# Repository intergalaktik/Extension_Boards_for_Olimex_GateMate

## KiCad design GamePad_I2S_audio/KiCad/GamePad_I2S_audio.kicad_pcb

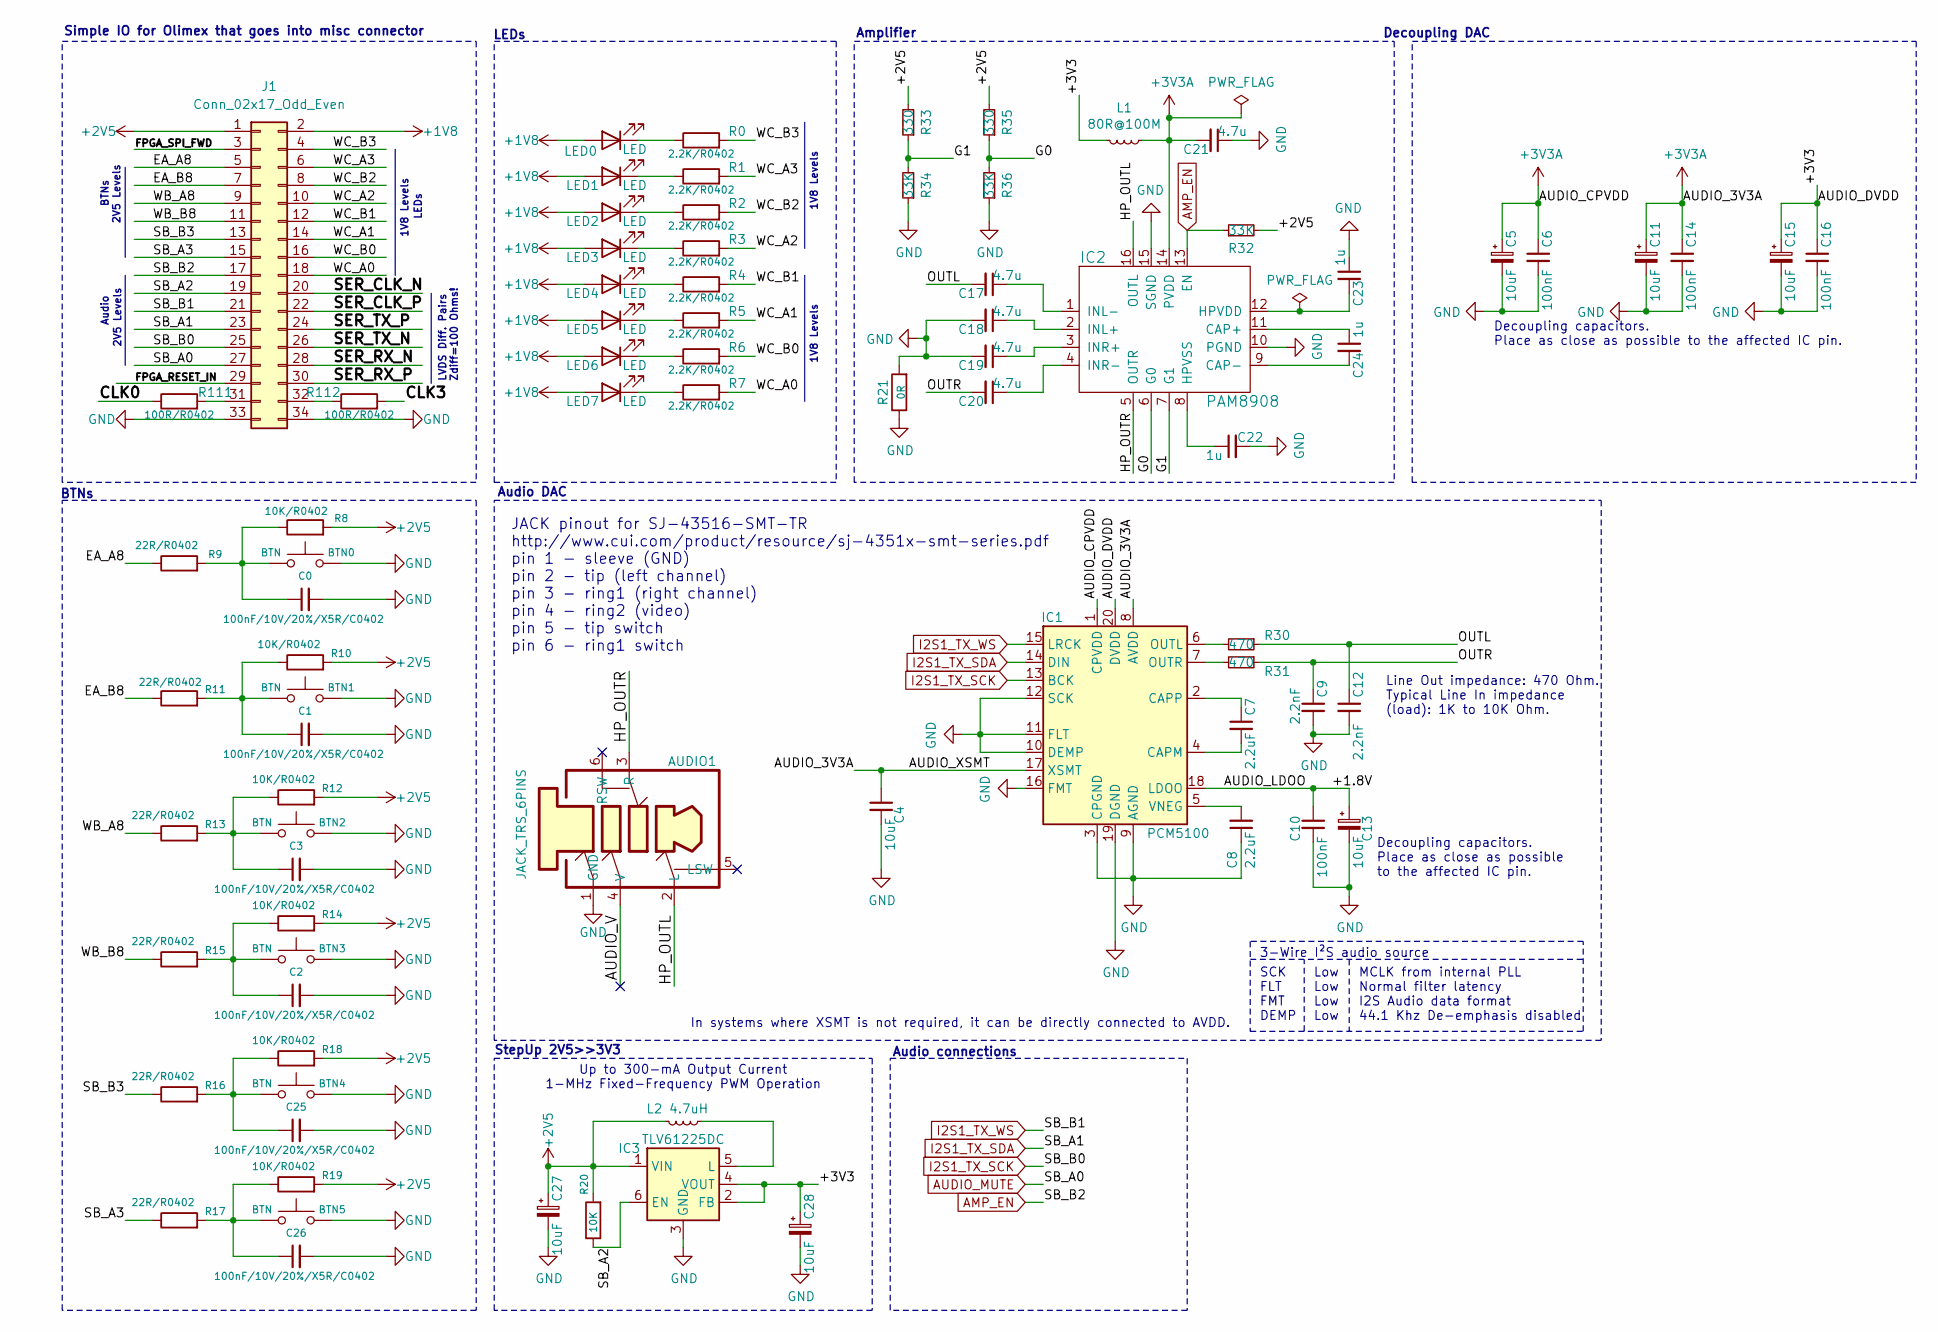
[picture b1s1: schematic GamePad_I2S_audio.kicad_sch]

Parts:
AUDIO1: JACK_TRS_6PINS; CUI_SJ-43516-SMT; MPN SJ-43516-SMT-TR; Mouser 490-SJ43515TS-SMT-TR
BTN0, BTN1, BTN2, BTN3, BTN4, BTN5: BTN; SW_SPST_B3S-1000
C0, C1, C2, C3, C25, C26: 100nF/10V/20%/X5R/C0402; C_0402_1005Metric
C4, C5, C11, C13, C15, C27, C28: 10uF; C_0603_1608Metric
C6, C10, C14, C16: 100nF; C_0402_1005Metric
C7, C8: 2.2uF; C_0402_1005Metric
C9, C12: 2.2nF; C_0402_1005Metric
C17, C18, C19, C20, C21: 4.7u; C_0603_1608Metric
C22, C23, C24: 1u; C_0603_1608Metric
IC1: PCM5100; TSSOP-20_4.4x6.5mm_P0.65mm
IC2: PAM8908; QFN-16-1EP_3x3mm_P0.5mm_EP1.7x1.7mm_ThermalVias
IC3: TLV61225DC; SOT-363_SC-70-6
J1: Conn_02x17_Odd_Even; PinSocket_2x17_P2.54mm_Vertical_SMD
L1: 80R@100M; L_0603_1608Metric
L2: 4.7uH; L_0603_1608Metric
LED0, LED1, LED2, LED3, LED4, LED5, LED6, LED7: LED; LED_0603_1608Metric
R0, R1, R2, R3, R4, R5, R6, R7: 2.2K/R0402; R_0402_1005Metric
R8, R10, R12, R14, R18, R19: 10K/R0402; R_0402_1005Metric
R9, R11, R13, R15, R16, R17: 22R/R0402; R_0402_1005Metric
R20: 10K; R_0402_1005Metric; MPN RC0603FR-071K1L; Digikey P1.10KHCT-ND
R21: 0R; R_0402_1005Metric
R30, R31: 470; R_0402_1005Metric
R32, R34, R36: 33K; R_0402_1005Metric
R33, R35: 330; R_0402_1005Metric
R111, R112: 100R/R0402; R_0402_1005Metric

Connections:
+1V8: J1.2, LED0.2 (A), LED1.2 (A), LED2.2 (A), LED3.2 (A), LED4.2 (A), LED5.2 (A), LED6.2 (A), LED7.2 (A)
+2V5: C27.1, IC3.1 (VIN), J1.1, L2.2, R8.2, R10.2, R12.2, R14.2, R18.2, R19.2, R20.2, R32.2, R33.2, R35.2
+3V3A: C4.1, C5.1, C6.1, C11.1, C14.1, C21.2, IC1.1 (CPVDD), IC1.8 (AVDD), IC1.17 (XSMT), IC2.14 (PVDD), L1.1
/+1.8V: C10.1, C13.1, IC1.18 (LDOO)
/+3V3: C15.1, C16.1, C28.1, IC1.20 (DVDD), IC3.2 (FB), IC3.4 (VOUT), L1.2
/AUDIO_V: AUDIO1.4 (V)
/CLK0: R111.1
/CLK3: R112.2
/EA_A8: J1.5, R9.1
/EA_B8: J1.7, R11.1
/FPGA_RESET_IN: J1.29
/FPGA_SPI_FWD: J1.3
/G0: IC2.6 (G0), R35.1, R36.2
/G1: IC2.7 (G1), R33.1, R34.2
/HP_OUTL: AUDIO1.2 (L), IC2.16 (OUTL)
/HP_OUTR: AUDIO1.3 (R), IC2.5 (OUTR)
/OUTL: C12.1, C17.2, R30.1
/OUTR: C9.1, C20.2, R31.1
/SB_A2: IC3.6 (EN), J1.19, R20.1
/SB_A3: J1.15, R17.1
/SB_B3: J1.13, R16.1
/SER_CLK_N: J1.20
/SER_CLK_P: J1.22
/SER_RX_N: J1.28
/SER_RX_P: J1.30
/SER_TX_N: J1.26
/SER_TX_P: J1.24
/WB_A8: J1.9, R13.1
/WB_B8: J1.11, R15.1
/WC_A0: J1.18, R7.2
/WC_A1: J1.14, R5.2
/WC_A2: J1.10, R3.2
/WC_A3: J1.6, R1.2
/WC_B0: J1.16, R6.2
/WC_B1: J1.12, R4.2
/WC_B2: J1.8, R2.2
/WC_B3: J1.4, R0.2
AMP_EN: IC2.13 (EN), J1.17, R32.1
AUDIO_MUTE: J1.27
I2S1_TX_SCK: IC1.13 (BCK), J1.25
I2S1_TX_SDA: IC1.14 (DIN), J1.23
I2S1_TX_WS: IC1.15 (LRCK), J1.21
unnamed: BTN0.1, C0.1, R8.1, R9.2
unnamed: BTN1.1, C1.1, R10.1, R11.2
unnamed: BTN2.1, C3.1, R12.1, R13.2
unnamed: BTN3.1, C2.1, R14.1, R15.2
unnamed: BTN4.1, C25.1, R16.2, R18.1
unnamed: BTN5.1, C26.1, R17.2, R19.1
unnamed: C7.2, IC1.4 (CAPM)
unnamed: C7.1, IC1.2 (CAPP)
unnamed: IC1.6 (OUTL), R30.2
unnamed: IC1.7 (OUTR), R31.2
unnamed: C8.2, IC1.5 (VNEG)
unnamed: C24.1, IC2.11 (CAP+)
unnamed: C24.2, IC2.9 (CAP-)
unnamed: C23.2, IC2.12 (HPVDD)
unnamed: C22.1, IC2.8 (HPVSS)
unnamed: C18.1, IC2.2 (INL+)
unnamed: C17.1, IC2.1 (INL-)
unnamed: C19.1, IC2.3 (INR+)
unnamed: C20.1, IC2.4 (INR-)
unnamed: IC3.5 (L), L2.1
unnamed: J1.31, R111.2
unnamed: J1.32, R112.1
unnamed: LED0.1 (K), R0.1
unnamed: LED1.1 (K), R1.1
unnamed: LED2.1 (K), R2.1
unnamed: LED3.1 (K), R3.1
unnamed: LED4.1 (K), R4.1
unnamed: LED5.1 (K), R5.1
unnamed: LED6.1 (K), R6.1
unnamed: LED7.1 (K), R7.1

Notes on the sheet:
2V5 Levels
1V8 Levels
Up to 300-mA Output Current 1-MHz Fixed-Frequency PWM Operation
Audio connections
Audio DAC
Line Out impedance: 470 Ohm. Typical Line In impedance (load): 1K to 10K Ohm.
StepUp 2V5>>3V3
BTNs
In systems where XSMT is not required, it can be directly connected to AVDD.
3-Wire I²S audio source
Low Low Low Low
Decoupling capacitors. Place as close as possible to the affected IC pin.
Amplifier
JACK pinout for SJ-43516-SMT-TR http://www.cui.com/product/resource/sj-4351x-smt-series.pdf pin 1 - sleeve (GND) pin 2 - tip (left channel) pin 3 - ring1 (right channel) pin 4 - ring2 (video) pin 5 - tip switch pin 6 - ring1 switch
LVDS Diff. Pairs Zdiff=100 Ohms!
SCK FLT FMT DEMP
MCLK from internal PLL Normal filter latency I2S Audio data format 44.1 Khz De-emphasis disabled
Audio
LEDs
Simple IO for Olimex that goes into misc connector
Decoupling capacitors. Place as close as possible to the affected IC pin.
Decoupling DAC

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
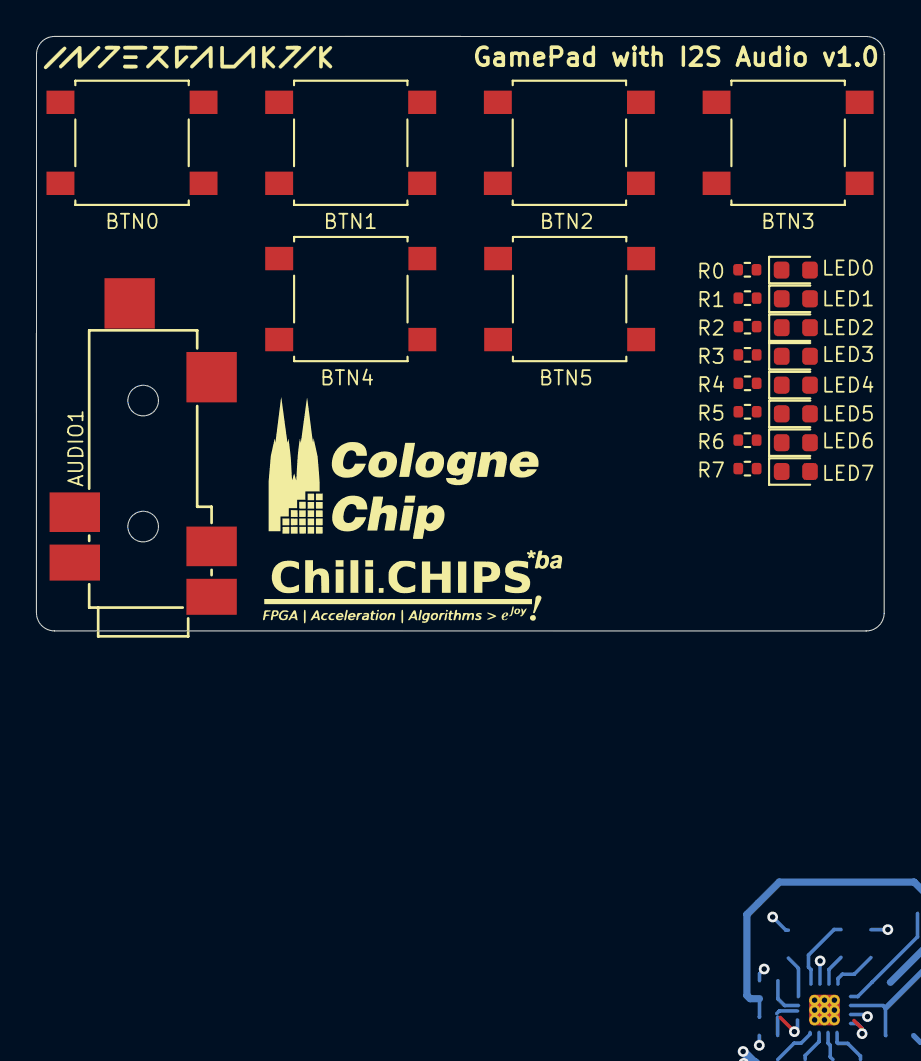
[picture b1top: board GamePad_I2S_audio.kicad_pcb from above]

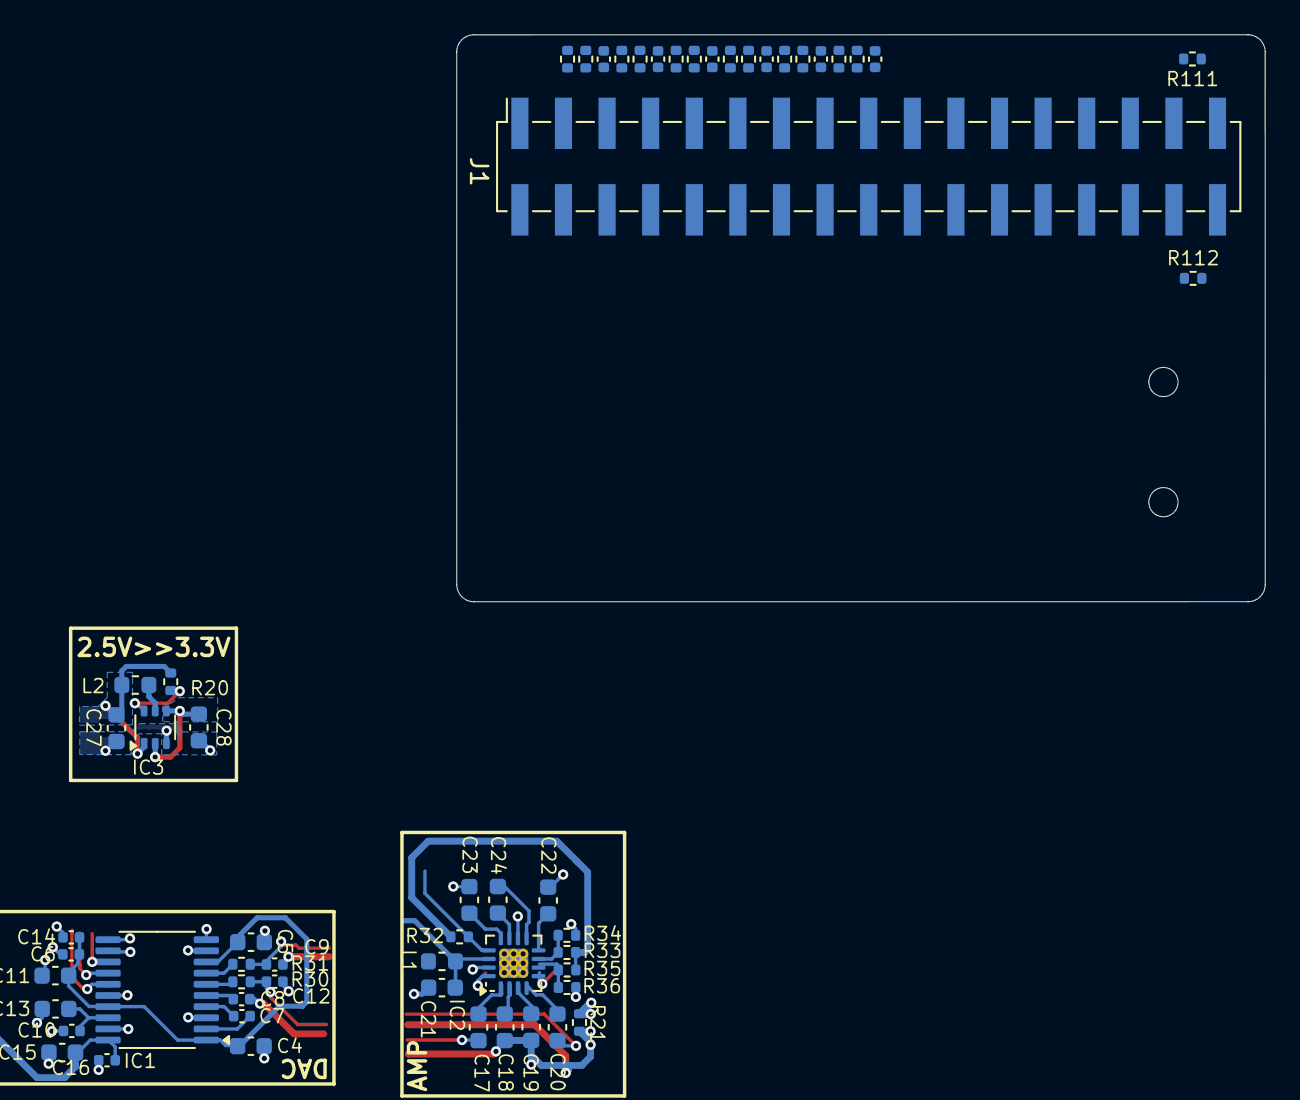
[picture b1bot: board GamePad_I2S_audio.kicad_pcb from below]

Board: 4 copper layers, 47.1 x 33.0 mm, 81 parts (58 on the bottom side), 62 nets.

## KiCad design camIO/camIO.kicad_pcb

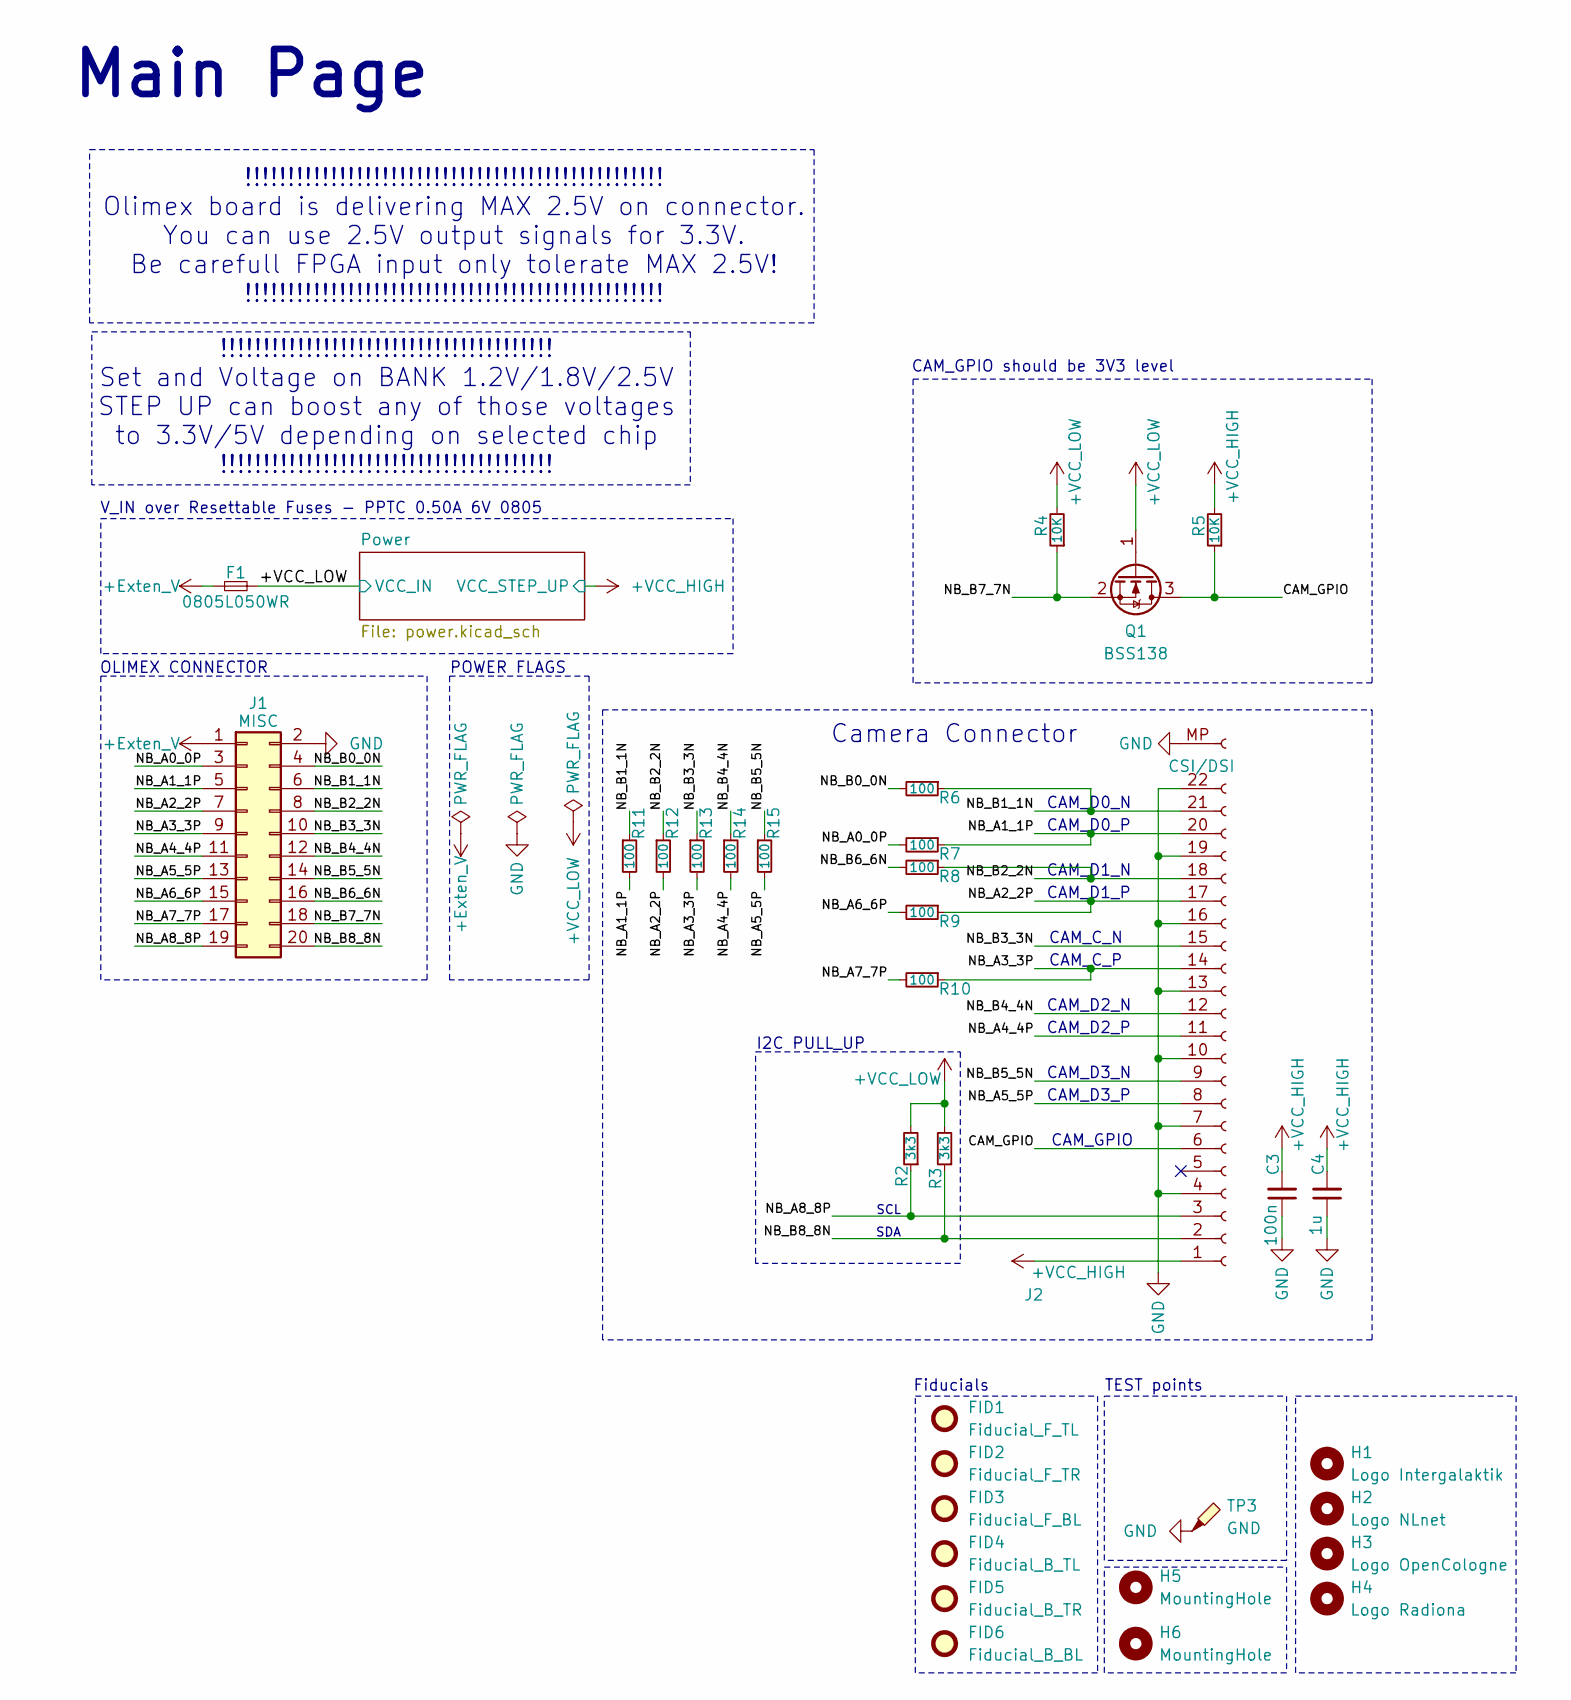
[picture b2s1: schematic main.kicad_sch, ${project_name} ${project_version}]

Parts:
C3: 100n; C_0402_1005Metric
C4: 1u; C_0603_1608Metric
F1: 0805L050WR; Fuse_0805_2012Metric
FID1: Fiducial_F_TL; Fiducial_0.5mm_Mask1mm
FID2: Fiducial_F_TR; Fiducial_0.5mm_Mask1mm
FID3: Fiducial_F_BL; Fiducial_0.5mm_Mask1mm
FID4: Fiducial_B_TL; Fiducial_0.5mm_Mask1mm
FID5: Fiducial_B_TR; Fiducial_0.5mm_Mask1mm
FID6: Fiducial_B_BL; Fiducial_0.5mm_Mask1mm
H1: Logo Intergalaktik; intergalaktik
H2: Logo NLnet; nlnet
H3: Logo OpenCologne; open_cologne_small
H4: Logo Radiona; radiona_small
H5, H6: MountingHole; MountingHole_2.2mm_M2
J1: MISC; PinSocket_2x10_P2.54mm_Vertical_SMD
J2: CSI/DSI; Hirose_FH12-22S-0.5SH_1x22-1MP_P0.50mm_Horizontal; Part Description 22 Position FFC, FPC Connector Contacts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
Q1: BSS138; SOT-23
R2, R3: 3k3; R_0402_1005Metric; MPN RC0603FR-071K1L; Mouser 603-RC0603FR-071K1L
R4, R5: 10K; R_0402_1005Metric; MPN RC0603FR-071K1L; Mouser 603-RC0603FR-071K1L
R6, R7, R8, R9, R10, R11, R12, R13, R14, R15: 100; R_0402_1005Metric; MPN RC0603FR-071K1L; Mouser 603-RC0603FR-071K1L
TP3: GND; TestPoint_Pad_D1.0mm

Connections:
+Exten_V: F1.1, J1.1
+VCC_HIGH: C3.2, C4.2, J2.1, R5.2; also elsewhere on the board
+VCC_LOW: F1.2, Q1.1 (G), R2.2, R3.2, R4.2; also elsewhere on the board
/Main Sheet/CAM_GPIO: J2.6, Q1.3 (D), R5.1
/Main Sheet/NB_A0_0P: J1.3, R7.2
/Main Sheet/NB_A1_1P: J1.5, J2.20, R7.1, R11.2
/Main Sheet/NB_A2_2P: J1.7, J2.17, R9.1, R12.2
/Main Sheet/NB_A3_3P: J1.9, J2.14, R10.1, R13.2
/Main Sheet/NB_A4_4P: J1.11, J2.11, R14.2
/Main Sheet/NB_A5_5P: J1.13, J2.8, R15.2
/Main Sheet/NB_A6_6P: J1.15, R9.2
/Main Sheet/NB_A7_7P: J1.17, R10.2
/Main Sheet/NB_A8_8P: J1.19, J2.3, R2.1
/Main Sheet/NB_B0_0N: J1.4, R6.2
/Main Sheet/NB_B1_1N: J1.6, J2.21, R6.1, R11.1
/Main Sheet/NB_B2_2N: J1.8, J2.18, R8.1, R12.1
/Main Sheet/NB_B3_3N: J1.10, J2.15, R13.1
/Main Sheet/NB_B4_4N: J1.12, J2.12, R14.1
/Main Sheet/NB_B5_5N: J1.14, J2.9, R15.1
/Main Sheet/NB_B6_6N: J1.16, R8.2
/Main Sheet/NB_B7_7N: J1.18, Q1.2 (S), R4.1
/Main Sheet/NB_B8_8N: J1.20, J2.2, R3.1
GND: C3.1, C4.1, J1.2, J2.4, J2.7, J2.10, J2.13, J2.16, J2.19, J2.22, J2.MP, TP3.1; also elsewhere on the board

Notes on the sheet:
Camera Connector
CAM_D1_N
TEST points
I2C PULL_UP
POWER FLAGS
V_IN over Resettable Fuses - PPTC 0.50A 6V 0805
!!!!!!!!!!!!!!!!!!!!!!!!!!!!!!!!!!!!!!!!!!!!!!!!! Olimex board is delivering MAX 2.5V on connector. You can use 2.5V output signals for 3.3V. Be carefull FPGA input only tolerate MAX 2.5V! !!!!!!!!!!!!!!!!!!!!!!!!!!!!!!!!!!!!!!!!!!!!!!!!!
CAM_D0_N
CAM_GPIO should be 3V3 level
CAM_D1_P
SCL
Fiducials
CAM_D0_P
CAM_D2_P
CAM_GPIO
CAM_D3_P
CAM_C_N
CAM_D2_N
OLIMEX CONNECTOR
CAM_D3_N
SDA
CAM_C_P
Main Page
!!!!!!!!!!!!!!!!!!!!!!!!!!!!!!!!!!!!!!! Set and Voltage on BANK 1.2V/1.8V/2.5V STEP UP can boost any of those voltages to 3.3V/5V depending on selected chip !!!!!!!!!!!!!!!!!!!!!!!!!!!!!!!!!!!!!!!

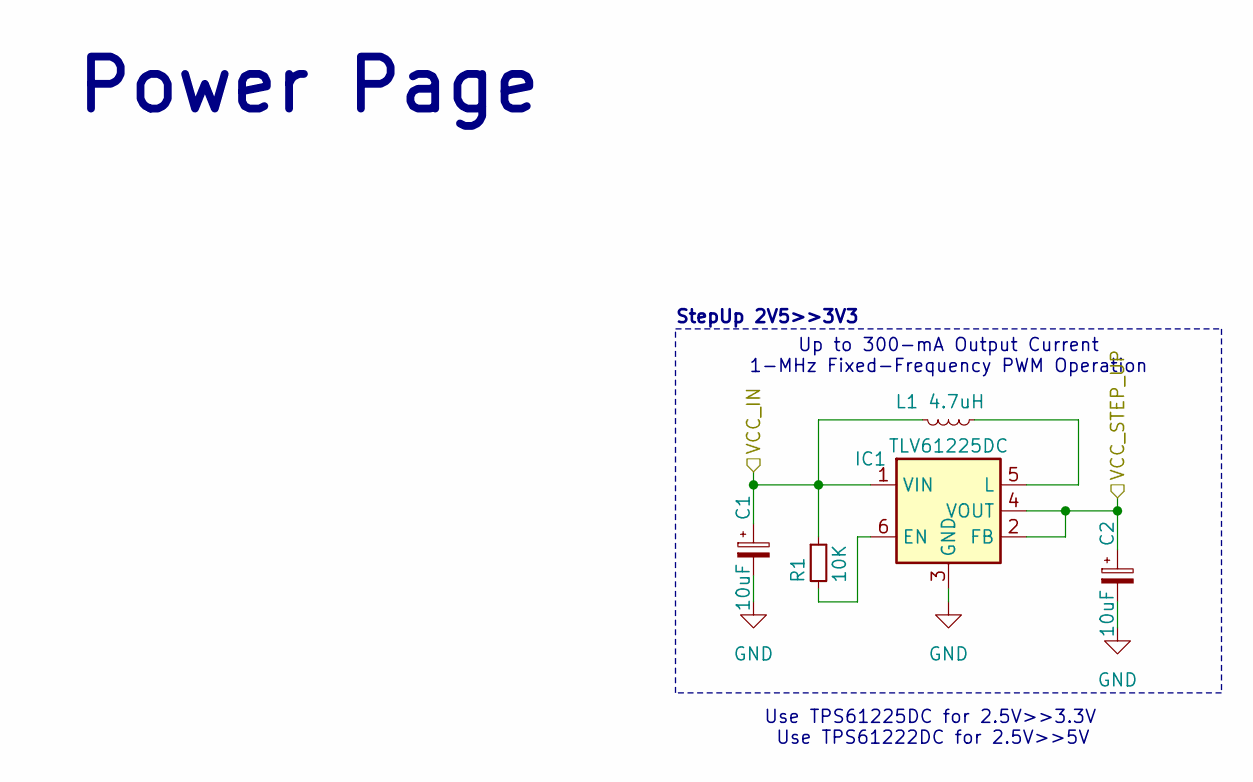
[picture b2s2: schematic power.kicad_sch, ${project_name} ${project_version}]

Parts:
C1, C2: 10uF; C_0603_1608Metric
IC1: TLV61225DC; SOT-363_SC-70-6
L1: 4.7uH; L_0603_1608Metric
R1: 10K; R_0402_1005Metric; MPN RC0603FR-071K1L; Mouser 603-RC0603FR-071K1L

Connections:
+VCC_HIGH: C2.1, IC1.2 (FB), IC1.4 (VOUT); also elsewhere on the board
+VCC_LOW: C1.1, IC1.1 (VIN), L1.2, R1.1; also elsewhere on the board
GND: C1.2, C2.2, IC1.3 (GND); also elsewhere on the board
unnamed: IC1.6 (EN), R1.2
unnamed: IC1.5 (L), L1.1

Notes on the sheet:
Up to 300-mA Output Current 1-MHz Fixed-Frequency PWM Operation
Use TPS61222DC for 2.5V>>5V
Power Page
StepUp 2V5>>3V3
Use TPS61225DC for 2.5V>>3.3V

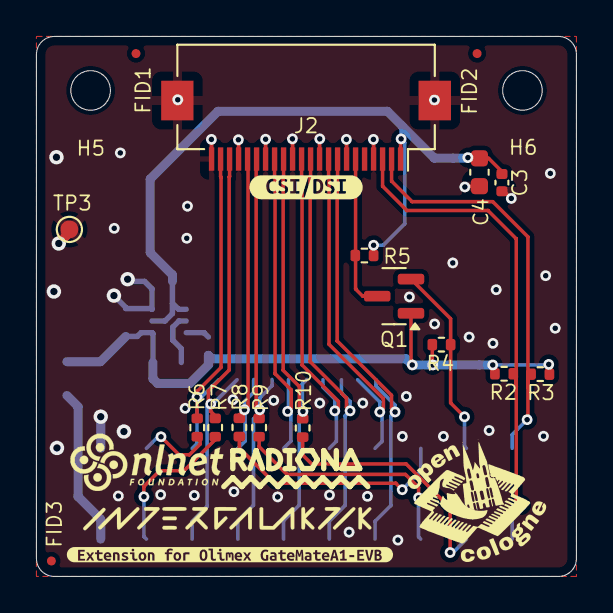
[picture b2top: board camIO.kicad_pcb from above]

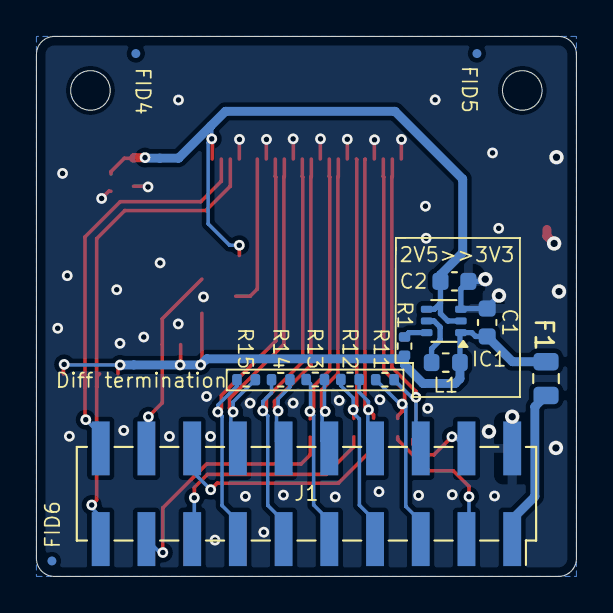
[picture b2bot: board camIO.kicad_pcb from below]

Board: 4 copper layers, 30.0 x 30.0 mm, 40 parts (15 on the bottom side), 25 nets.

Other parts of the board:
kibuzzard-674D68C8: G***; kibuzzard-674D68C8
kibuzzard-67584A5F: G***; kibuzzard-67584A5F

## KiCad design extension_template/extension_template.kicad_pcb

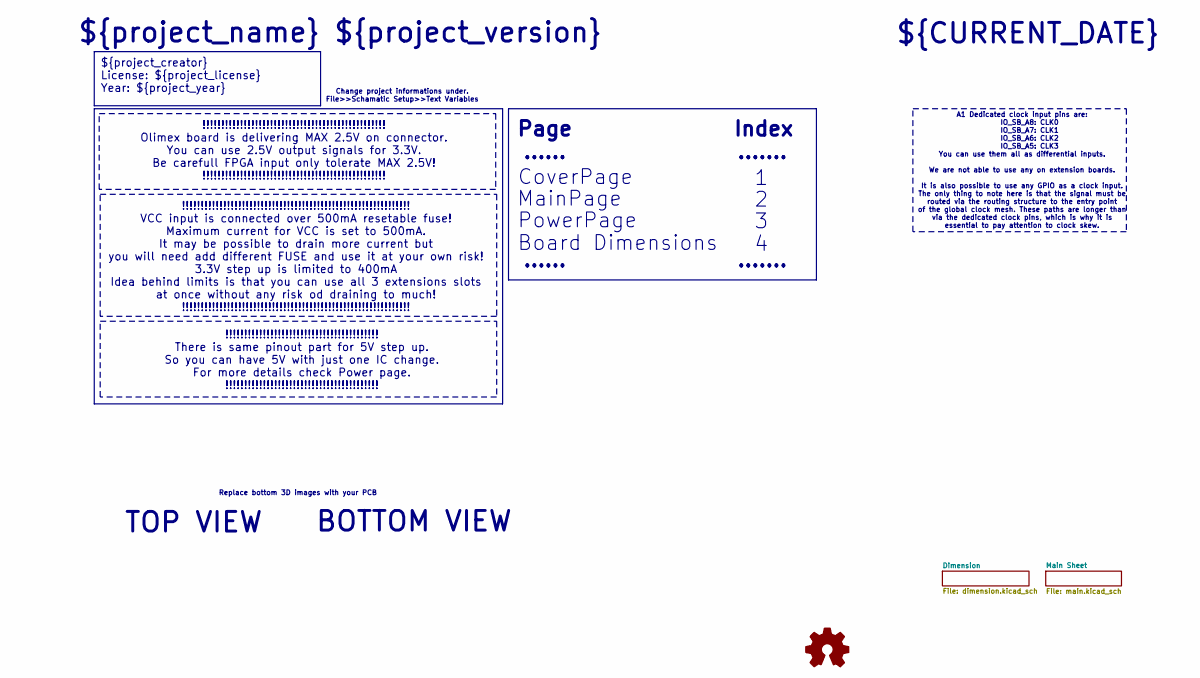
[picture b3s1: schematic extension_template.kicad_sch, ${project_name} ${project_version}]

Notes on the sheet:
${project_creator} License: ${project_license} Year: ${project_year}
BOTTOM VIEW
Replace bottom 3D images with your PCB
Index
!!!!!!!!!!!!!!!!!!!!!!!!!!!!!!!!!!!!!!!!!!!!!!!!!!!!!!!!!!!!! VCC input is connected over 500mA resetable fuse! Maximum current for VCC is set to 500mA. It may be possible to drain more current but you will need add different FUSE and use it at your own risk! 3.3V step up is limited to 400mA Idea b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
!!!!!!!!!!!!!!!!!!!!!!!!!!!!!!!!!!!!!!!!!!!!!!!!! Olimex board is delivering MAX 2.5V on connector. You can use 2.5V output signals for 3.3V. Be carefull FPGA input only tolerate MAX 2.5V! !!!!!!!!!!!!!!!!!!!!!!!!!!!!!!!!!!!!!!!!!!!!!!!!!
!!!!!!!!!!!!!!!!!!!!!!!!!!!!!!!!!!!!!!!!! There is same pinout part for 5V step up. So you can have 5V with just one IC change. For more details check Power page. !!!!!!!!!!!!!!!!!!!!!!!!!!!!!!!!!!!!!!!!!
......
PowerPage
Change project informations under. File>>Schamatic Setup>>Text Variables
.......
A1 Dedicated clock input pins are: IO_SB_A8: CLK0 IO_SB_A7: CLK1 IO_SB_A6: CLK2 IO_SB_A5: CLK3 You can use them all as differential inputs. We are not able to use any on extension boards. It is also possible to use any GPIO as a clock input. The only thing to note here is that the signal must be ro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
CoverPage
Board Dimensions
MainPage
${CURRENT_DATE}
${project_name} ${project_version}
TOP VIEW
Page

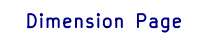
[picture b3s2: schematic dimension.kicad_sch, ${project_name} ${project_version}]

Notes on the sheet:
Dimension Page

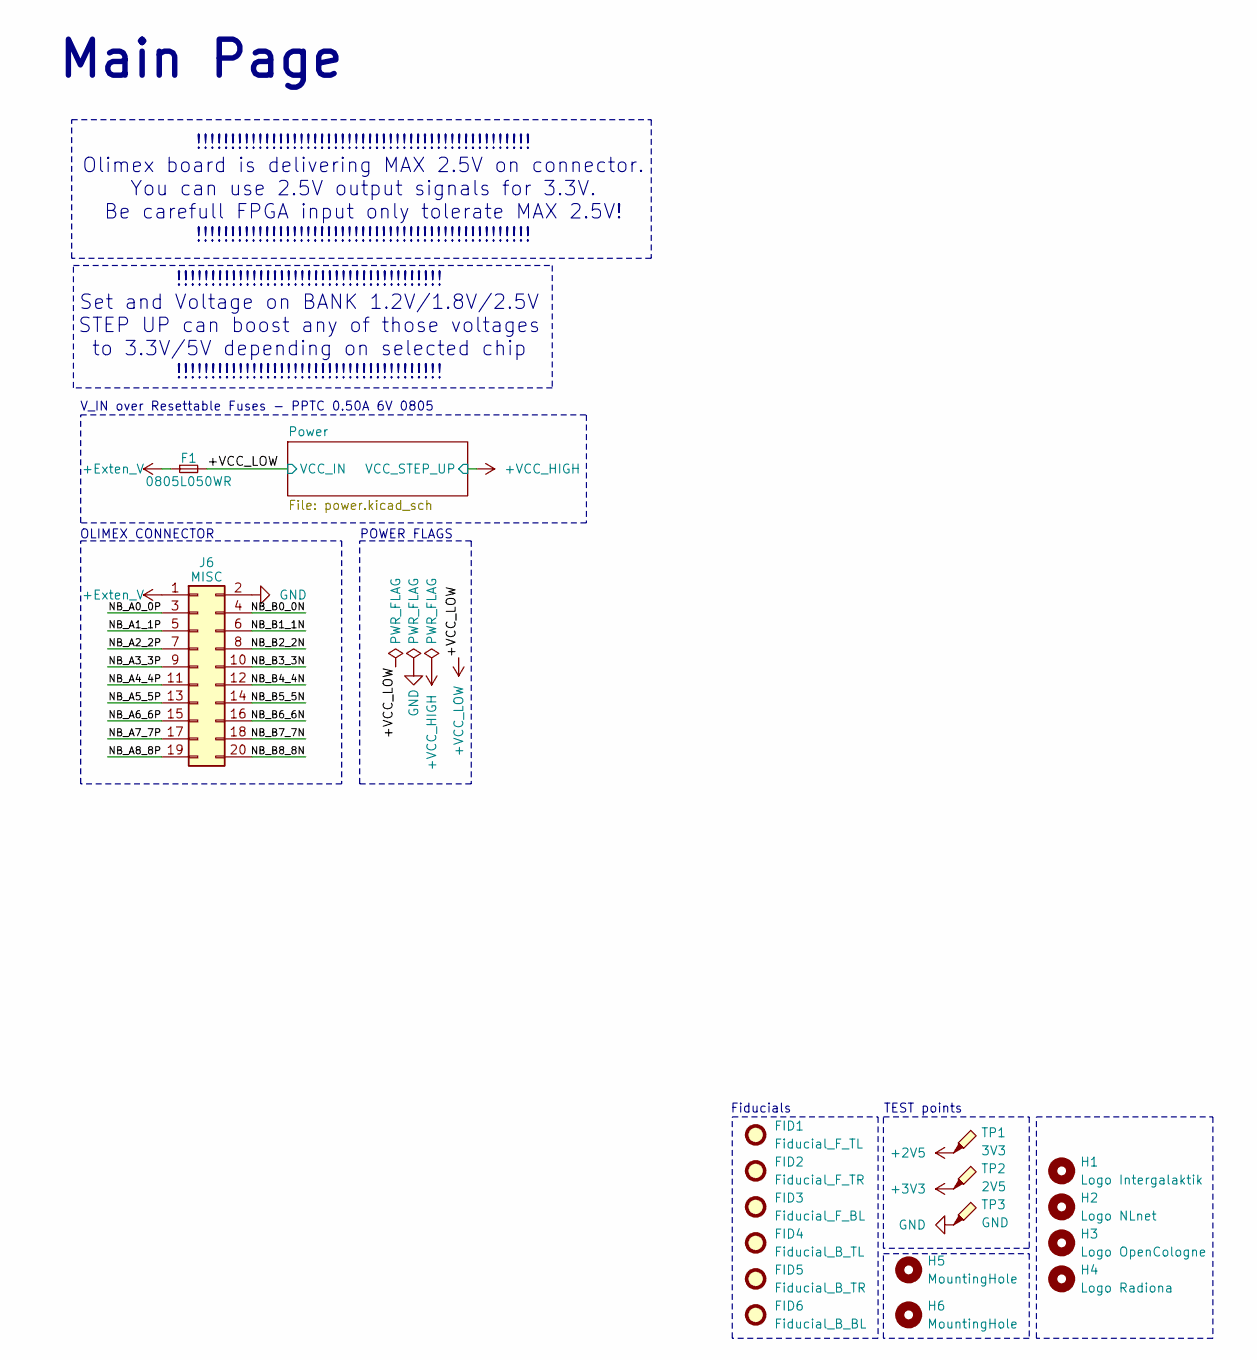
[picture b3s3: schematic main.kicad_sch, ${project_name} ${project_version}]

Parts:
F1: 0805L050WR; Fuse_0805_2012Metric
FID1: Fiducial_F_TL; Fiducial_0.5mm_Mask1mm
FID2: Fiducial_F_TR; Fiducial_0.5mm_Mask1mm
FID3: Fiducial_F_BL; Fiducial_0.5mm_Mask1mm
FID4: Fiducial_B_TL; Fiducial_0.5mm_Mask1mm
FID5: Fiducial_B_TR; Fiducial_0.5mm_Mask1mm
FID6: Fiducial_B_BL; Fiducial_0.5mm_Mask1mm
H1: Logo Intergalaktik; intergalaktik
H2: Logo NLnet; nlnet
H3: Logo OpenCologne; open_cologne_small
H4: Logo Radiona; radiona_small
H5, H6: MountingHole; MountingHole_2.2mm_M2
J6: MISC; PinSocket_2x10_P2.54mm_Vertical_SMD
TP1: 3V3; TestPoint_Pad_D1.0mm
TP2: 2V5; TestPoint_Pad_D1.0mm
TP3: GND; TestPoint_Pad_D1.0mm

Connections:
+2V5: F1.2, TP1.1; also elsewhere on the board
+3V3: TP2.1; also elsewhere on the board
+Exten_V: F1.1, J6.1
/Main Sheet/NB_A0: J6.3
/Main Sheet/NB_A1: J6.5
/Main Sheet/NB_A2: J6.7
/Main Sheet/NB_A3: J6.9
/Main Sheet/NB_A4: J6.11
/Main Sheet/NB_A5: J6.13
/Main Sheet/NB_A6: J6.15
/Main Sheet/NB_A7: J6.17
/Main Sheet/NB_A8: J6.19
/Main Sheet/NB_B0: J6.4
/Main Sheet/NB_B1: J6.6
/Main Sheet/NB_B2: J6.8
/Main Sheet/NB_B3: J6.10
/Main Sheet/NB_B4: J6.12
/Main Sheet/NB_B5: J6.14
/Main Sheet/NB_B6: J6.16
/Main Sheet/NB_B7: J6.18
/Main Sheet/NB_B8: J6.20
GND: J6.2, TP3.1; also elsewhere on the board

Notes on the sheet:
TEST points
POWER FLAGS
V_IN over Resettable Fuses - PPTC 0.50A 6V 0805
!!!!!!!!!!!!!!!!!!!!!!!!!!!!!!!!!!!!!!!!!!!!!!!!! Olimex board is delivering MAX 2.5V on connector. You can use 2.5V output signals for 3.3V. Be carefull FPGA input only tolerate MAX 2.5V! !!!!!!!!!!!!!!!!!!!!!!!!!!!!!!!!!!!!!!!!!!!!!!!!!
Fiducials
OLIMEX CONNECTOR
Main Page
!!!!!!!!!!!!!!!!!!!!!!!!!!!!!!!!!!!!!!! Set and Voltage on BANK 1.2V/1.8V/2.5V STEP UP can boost any of those voltages to 3.3V/5V depending on selected chip !!!!!!!!!!!!!!!!!!!!!!!!!!!!!!!!!!!!!!!

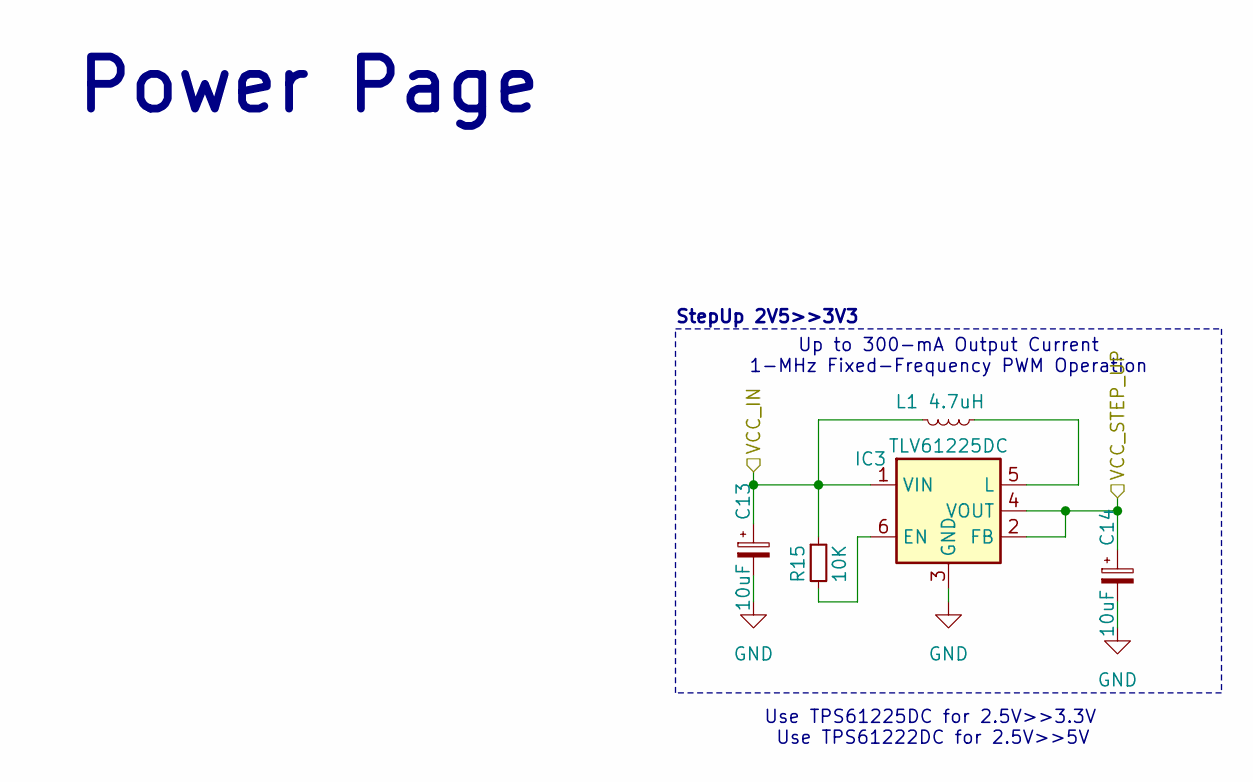
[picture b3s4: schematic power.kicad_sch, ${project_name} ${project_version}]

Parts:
C13, C14: 10uF; C_0603_1608Metric
IC3: TLV61225DC; SOT-363_SC-70-6
L1: 4.7uH; L_0603_1608Metric
R15: 10K; R_0402_1005Metric; MPN RC0603FR-071K1L; Mouser 603-RC0603FR-071K1L

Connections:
+2V5: C13.1, IC3.1 (VIN), L1.2, R15.1; also elsewhere on the board
+3V3: C14.1, IC3.2 (FB), IC3.4 (VOUT); also elsewhere on the board
GND: C13.2, C14.2, IC3.3 (GND); also elsewhere on the board
unnamed: IC3.6 (EN), R15.2
unnamed: IC3.5 (L), L1.1

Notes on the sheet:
Up to 300-mA Output Current 1-MHz Fixed-Frequency PWM Operation
Use TPS61222DC for 2.5V>>5V
Power Page
StepUp 2V5>>3V3
Use TPS61225DC for 2.5V>>3.3V

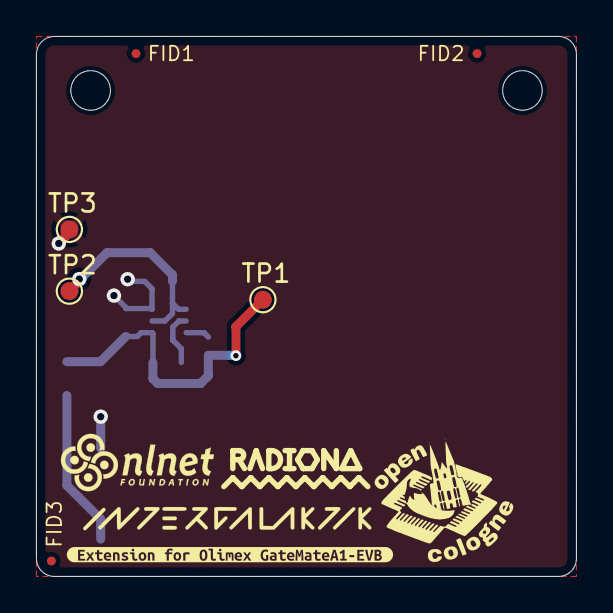
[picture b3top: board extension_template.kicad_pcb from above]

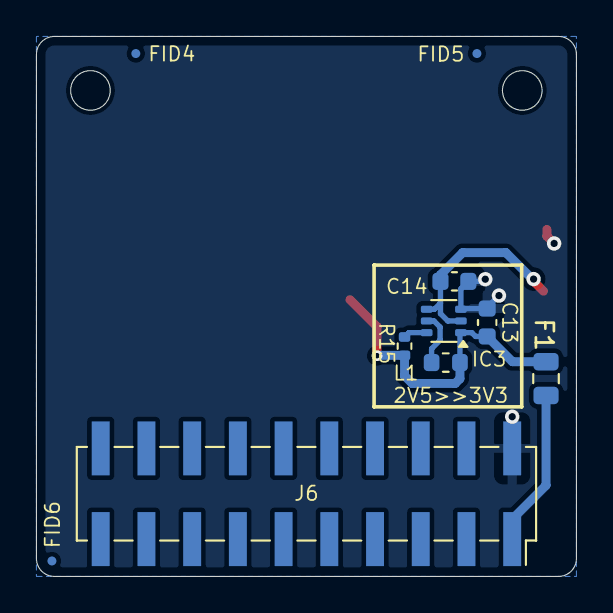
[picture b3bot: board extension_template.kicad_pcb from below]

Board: 4 copper layers, 30.0 x 30.0 mm, 23 parts (10 on the bottom side), 6 nets.

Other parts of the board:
kibuzzard-674D68C8: G***; kibuzzard-674D68C8

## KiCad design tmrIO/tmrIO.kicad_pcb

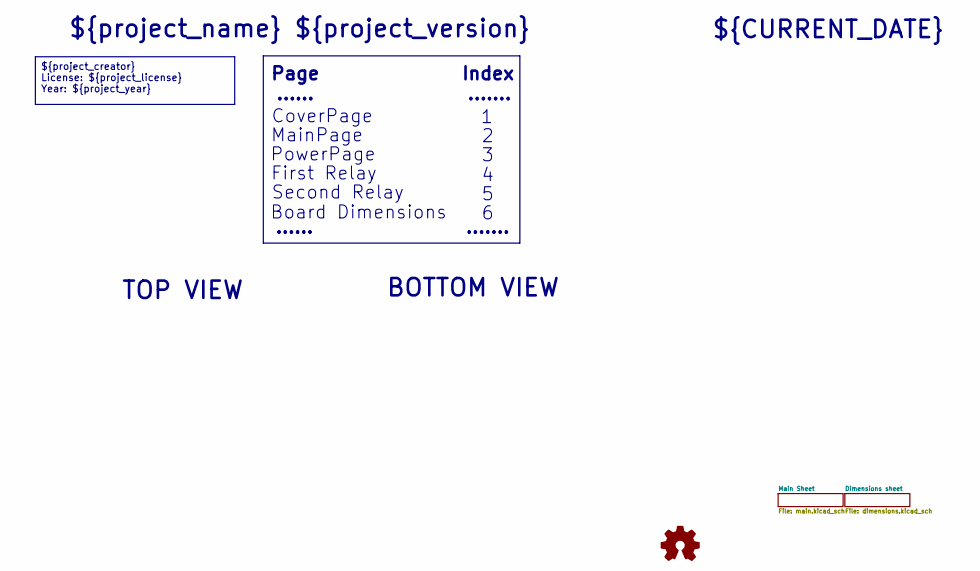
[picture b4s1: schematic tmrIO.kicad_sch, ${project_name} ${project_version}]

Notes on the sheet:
${project_creator} License: ${project_license} Year: ${project_year}
BOTTOM VIEW
Index
First Relay
......
PowerPage
.......
CoverPage
Board Dimensions
Second Relay
MainPage
${CURRENT_DATE}
${project_name} ${project_version}
TOP VIEW
Page

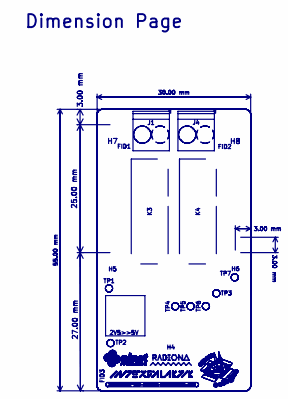
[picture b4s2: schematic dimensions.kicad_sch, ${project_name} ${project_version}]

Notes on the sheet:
Dimension Page

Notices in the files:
GamePad_I2S_audio/KiCad/GamePad_I2S_audio.kicad_sch:
CERN-OHL-S v2
parts and their libraries:
project_license: CERN-OHL-S v2
